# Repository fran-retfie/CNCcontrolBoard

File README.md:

# CNCcontrolBoard
CNC Control and Pendant Board with USB, RS485, SDCARD and LCD

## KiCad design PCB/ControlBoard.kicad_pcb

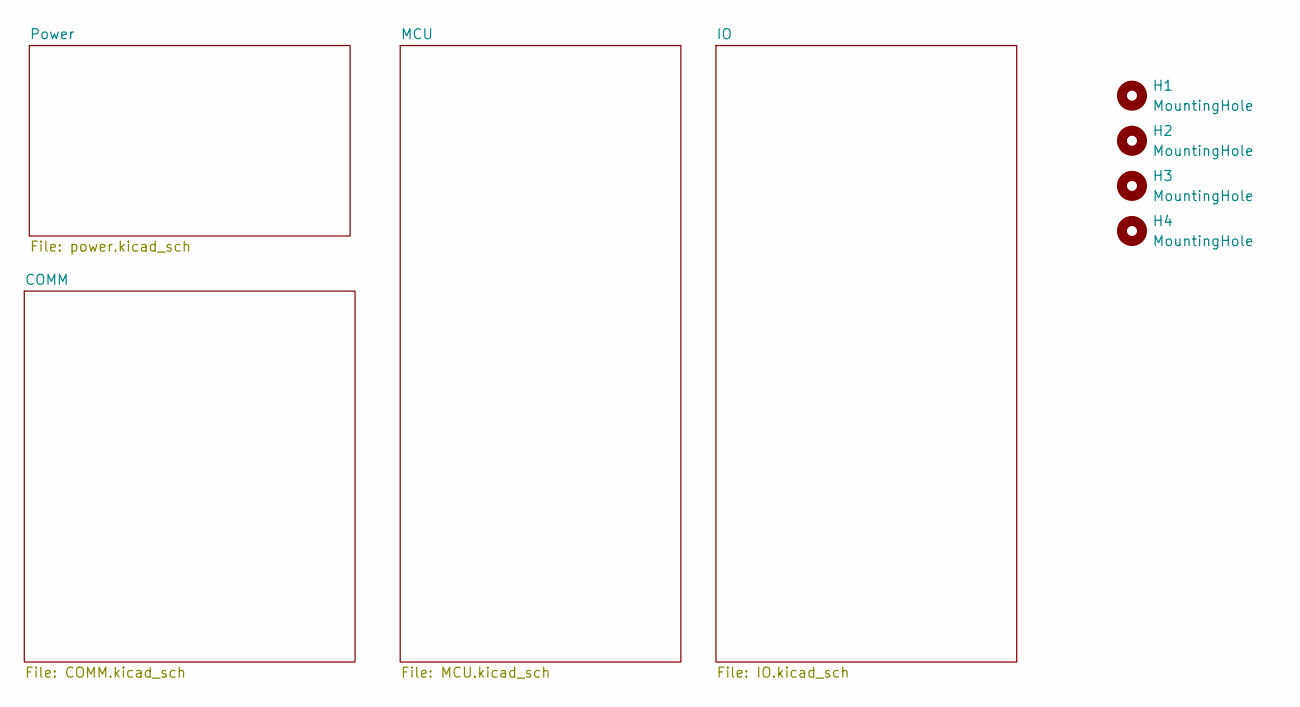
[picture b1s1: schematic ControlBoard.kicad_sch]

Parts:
H1, H2, H3, H4: MountingHole; MountingHole_3.2mm_M3_ISO14580_Pad

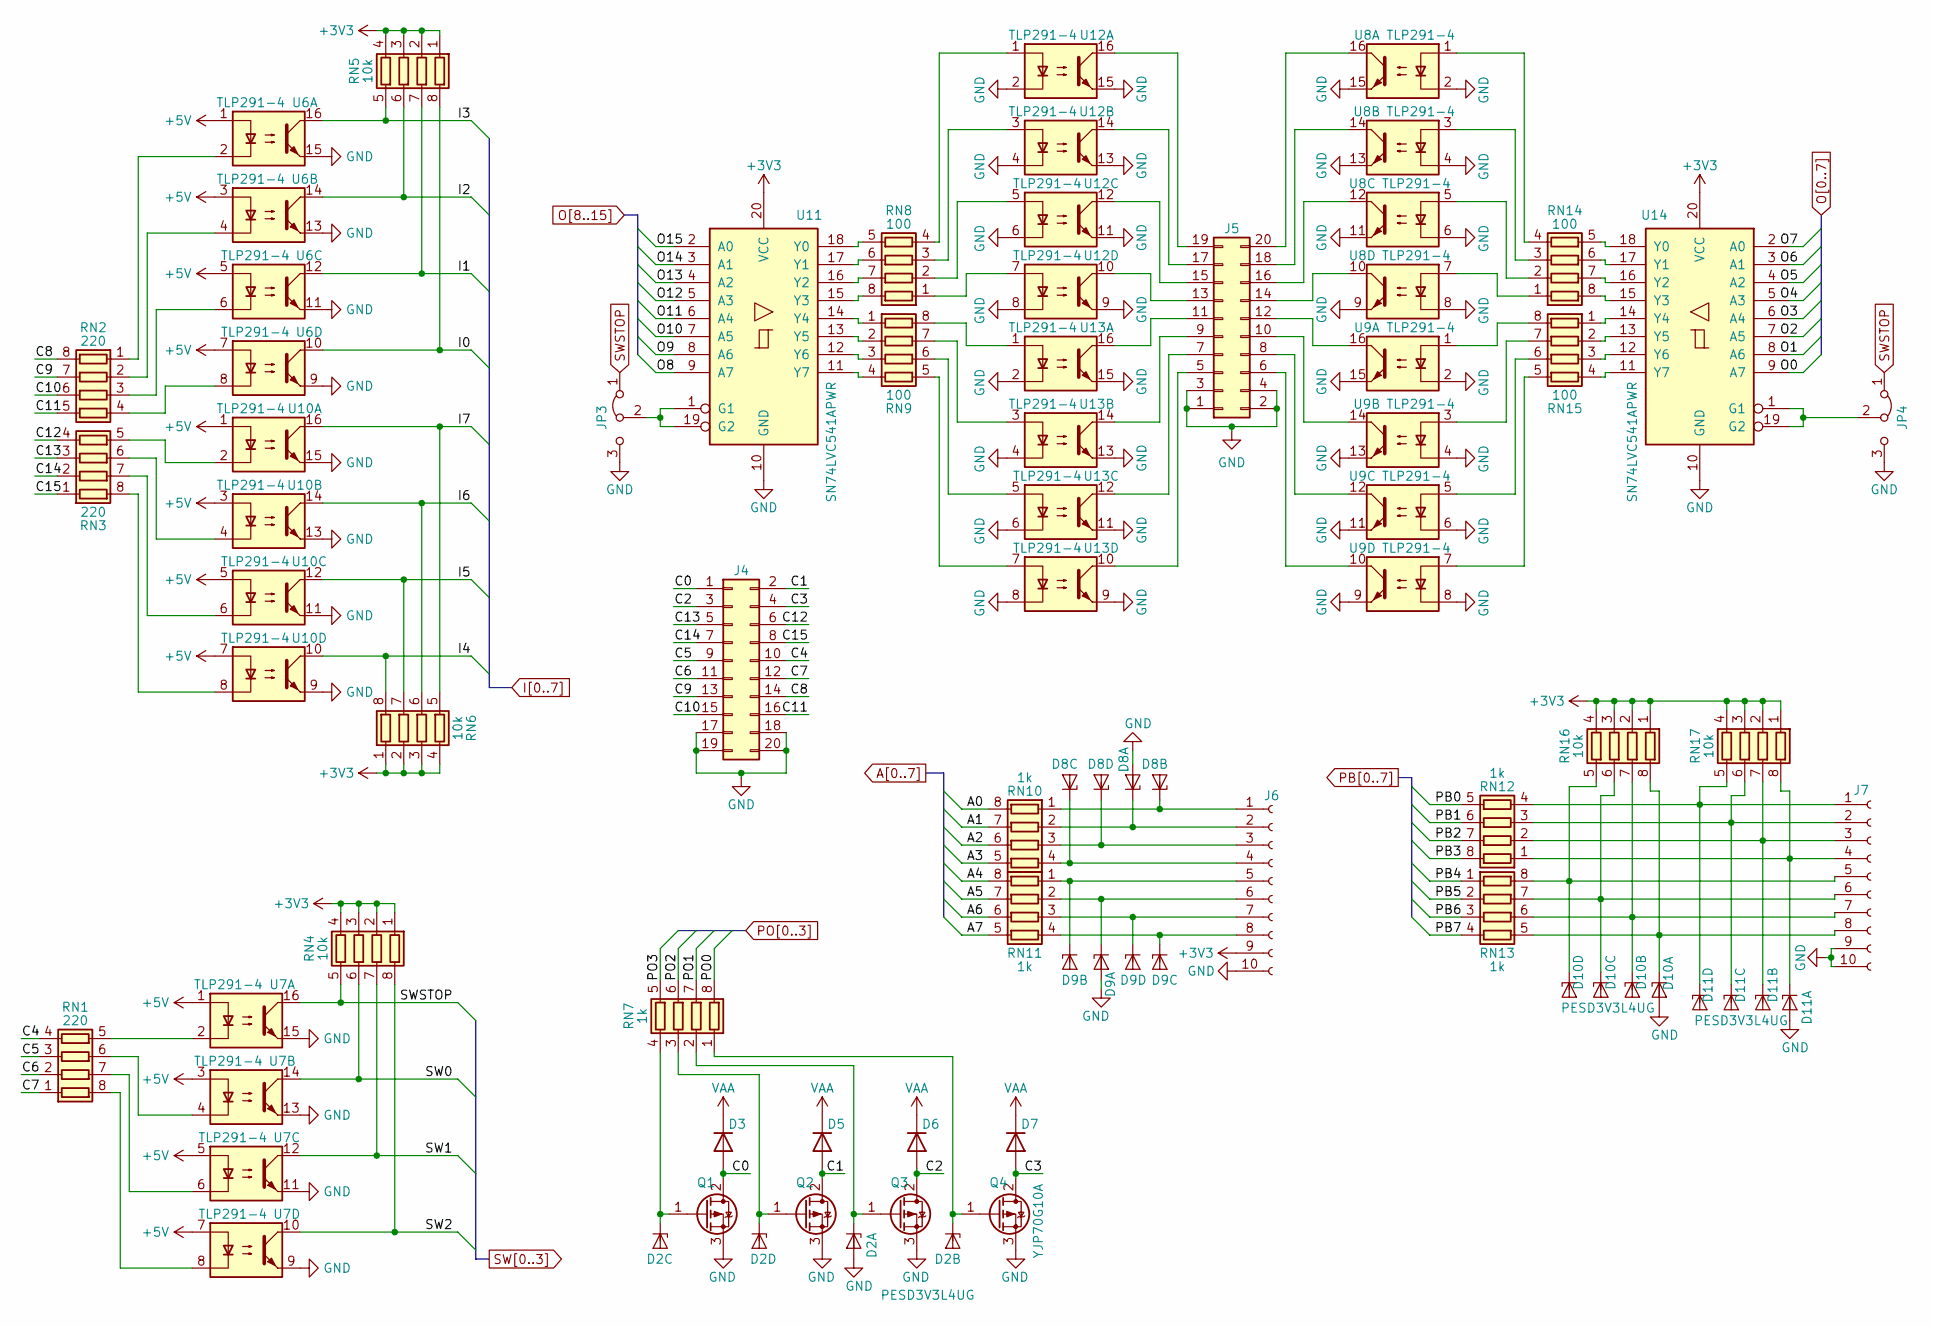
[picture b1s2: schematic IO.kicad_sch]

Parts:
D2, D10, D11: PESD3V3L4UG; SOT-353_SC-70-5; LCSC C3021134
D3, D5, D6, D7: M7; D_SMA; LCSC C95872
D8, D9: w; SOT-353_SC-70-5; LCSC C3021134
J4, J5: Conn_02x10_Odd_Even; DIP-20_500_ELL; LCSC C48336
J6, J7: Conn_01x10_Female; PinHeader_2x05_P2.54mm_Vertical
JP3: Jumper_3_Bridged12; SolderJumper-3_P1.3mm_Bridged12_RoundedPad1.0x1.5mm
JP4: Jumper_3_Bridged12; SolderJumper-3_P1.3mm_Bridged2Bar12_RoundedPad1.0x1.5mm
Q1, Q2, Q3, Q4: YJP70G10A; TO-220-3_Vertical
RN1, RN2, RN3: 220; R_Array_Concave_4x0603
RN4, RN5, RN6, RN16, RN17: 10k; R_Array_Concave_4x0603
RN7, RN10, RN11, RN12, RN13: 1k; R_Array_Concave_4x0603
RN8, RN9, RN14, RN15: 100; R_Array_Concave_4x0603
U6, U8, U9, U10, U12, U13: TLP291-4; SOIC-16_4.55x10.3mm_P1.27mm; LCSC C60900
U7: TLP291-4; SOIC-16_4.55x10.3mm_P1.27mm
U11, U14: SN74LVC541APWR; TSSOP-20_4.4x6.5mm_P0.65mm; LCSC C113281

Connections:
+3V3: J6.9, RN4.1 (R1.1), RN4.2 (R2.1), RN4.3 (R3.1), RN4.4 (R4.1), RN5.1 (R1.1), RN5.2 (R2.1), RN5.3 (R3.1), RN5.4 (R4.1), RN6.1 (R1.1), RN6.2 (R2.1), RN6.3 (R3.1), RN6.4 (R4.1), RN16.1 (R1.1), RN16.2 (R2.1), RN16.3 (R3.1), RN16.4 (R4.1), RN17.1 (R1.1), RN17.2 (R2.1), RN17.3 (R3.1), RN17.4 (R4.1), U11.20 (VCC), U14.20 (VCC); also elsewhere on the board
+5V: U6.1, U6.3, U6.5, U6.7, U7.1, U7.3, U7.5, U7.7, U10.1, U10.3, U10.5, U10.7; also elsewhere on the board
/IO/C0: D3.2 (A), J4.1, Q1.2 (D)
/IO/C1: D5.2 (A), J4.2, Q2.2 (D)
/IO/C2: D6.2 (A), J4.3, Q3.2 (D)
/IO/C3: D7.2 (A), J4.4, Q4.2 (D)
/IO/C4: J4.10, RN1.4 (R4.1)
/IO/C5: J4.9, RN1.3 (R3.1)
/IO/C6: J4.11, RN1.2 (R2.1)
/IO/C7: J4.12, RN1.1 (R1.1)
/IO/C8: J4.14, RN2.8 (R1.2)
/IO/C9: J4.13, RN2.7 (R2.2)
/IO/C10: J4.15, RN2.6 (R3.2)
/IO/C11: J4.16, RN2.5 (R4.2)
/IO/C12: J4.6, RN3.4 (R4.1)
/IO/C13: J4.5, RN3.3 (R3.1)
/IO/C14: J4.7, RN3.2 (R2.1)
/IO/C15: J4.8, RN3.1 (R1.1)
A0: RN10.8 (R1.2); also elsewhere on the board
A1: RN10.7 (R2.2); also elsewhere on the board
A2: RN10.6 (R3.2); also elsewhere on the board
A3: RN10.5 (R4.2); also elsewhere on the board
A4: RN11.8 (R1.2); also elsewhere on the board
A5: RN11.7 (R2.2); also elsewhere on the board
A6: RN11.6 (R3.2); also elsewhere on the board
A7: RN11.5 (R4.2); also elsewhere on the board
GND: D2.2 (A), D8.2 (A), D9.2 (A), D10.2 (A), D11.2 (A), J4.17, J4.18, J4.19, J4.20, J5.1, J5.2, J5.3, J5.4, J6.10, J7.9, J7.10, JP3.3 (B), JP4.3 (B), Q1.3 (S), Q2.3 (S), Q3.3 (S), Q4.3 (S), U6.9, U6.11, U6.13, U6.15, U7.9, U7.11, U7.13, U7.15, U8.2, U8.4, U8.6, U8.8, U8.9, U8.11, U8.13, U8.15, U9.2, U9.4, U9.6, U9.8, U9.9, U9.11, U9.13, U9.15, U10.9, U10.11, U10.13, U10.15, U11.10 (GND), U12.2, U12.4, U12.6, U12.8, U12.9, U12.11, U12.13, U12.15, U13.2, U13.4, U13.6, U13.8, U13.9, U13.11, U13.13, U13.15, U14.10 (GND); also elsewhere on the board
I0: RN5.8 (R1.2), U6.10; also elsewhere on the board
I1: RN5.7 (R2.2), U6.12; also elsewhere on the board
I2: RN5.6 (R3.2), U6.14; also elsewhere on the board
I3: RN5.5 (R4.2), U6.16; also elsewhere on the board
I4: RN6.8 (R1.2), U10.10; also elsewhere on the board
I5: RN6.7 (R2.2), U10.12; also elsewhere on the board
I6: RN6.6 (R3.2), U10.14; also elsewhere on the board
I7: RN6.5 (R4.2), U10.16; also elsewhere on the board
unnamed: D2.1 (K1), Q3.1 (G), RN7.2 (R2.1)
unnamed: D2.3 (K2), Q4.1 (G), RN7.1 (R1.1)
unnamed: D2.4 (K3), Q1.1 (G), RN7.4 (R4.1)
unnamed: D2.5 (K4), Q2.1 (G), RN7.3 (R3.1)
unnamed: D8.1 (K1), J6.2, RN10.2 (R2.1)
unnamed: D8.3 (K2), J6.1, RN10.1 (R1.1)
unnamed: D8.4 (K3), J6.4, RN10.4 (R4.1)
unnamed: D8.5 (K4), J6.3, RN10.3 (R3.1)
unnamed: D9.1 (K1), J6.6, RN11.2 (R2.1)
unnamed: D9.3 (K2), J6.5, RN11.1 (R1.1)
unnamed: D9.4 (K3), J6.8, RN11.4 (R4.1)
unnamed: D9.5 (K4), J6.7, RN11.3 (R3.1)
unnamed: D10.1 (K1), J7.8, RN13.5 (R4.2), RN16.8 (R1.2)
unnamed: D10.3 (K2), J7.7, RN13.6 (R3.2), RN16.7 (R2.2)
unnamed: D10.4 (K3), J7.6, RN13.7 (R2.2), RN16.6 (R3.2)
unnamed: D10.5 (K4), J7.5, RN13.8 (R1.2), RN16.5 (R4.2)
unnamed: D11.1 (K1), J7.4, RN12.1 (R1.1), RN17.8 (R1.2)
unnamed: D11.3 (K2), J7.3, RN12.2 (R2.1), RN17.7 (R2.2)
unnamed: D11.4 (K3), J7.2, RN12.3 (R3.1), RN17.6 (R3.2)
unnamed: D11.5 (K4), J7.1, RN12.4 (R4.1), RN17.5 (R4.2)
unnamed: J5.5, U13.10
unnamed: J5.6, U9.10
unnamed: J5.7, U13.12
unnamed: J5.8, U9.12
unnamed: J5.9, U13.14
unnamed: J5.10, U9.14
unnamed: J5.11, U13.16
unnamed: J5.12, U9.16
unnamed: J5.13, U12.10
unnamed: J5.14, U8.10
unnamed: J5.15, U12.12
unnamed: J5.16, U8.12
unnamed: J5.17, U12.14
unnamed: J5.18, U8.14
unnamed: J5.19, U12.16
unnamed: J5.20, U8.16
unnamed: JP3.2 (C), U11.1 (G1), U11.19 (G2)
unnamed: JP4.2 (C), U14.1 (G1), U14.19 (G2)
unnamed: RN1.5 (R4.2), U7.2
unnamed: RN1.6 (R3.2), U7.4
unnamed: RN1.7 (R2.2), U7.6
unnamed: RN1.8 (R1.2), U7.8
unnamed: RN2.1 (R1.1), U6.2
unnamed: RN2.2 (R2.1), U6.4
unnamed: RN2.3 (R3.1), U6.6
unnamed: RN2.4 (R4.1), U6.8
unnamed: RN3.5 (R4.2), U10.2
unnamed: RN3.6 (R3.2), U10.4
unnamed: RN3.7 (R2.2), U10.6
unnamed: RN3.8 (R1.2), U10.8
unnamed: RN8.1 (R1.1), U12.7
unnamed: RN8.2 (R2.1), U12.5
unnamed: RN8.3 (R3.1), U12.3
unnamed: RN8.4 (R4.1), U12.1
unnamed: RN8.5 (R4.2), U11.18 (Y0)
unnamed: RN8.6 (R3.2), U11.17 (Y1)
unnamed: RN8.7 (R2.2), U11.16 (Y2)
unnamed: RN8.8 (R1.2), U11.15 (Y3)
unnamed: RN9.1 (R1.1), U11.14 (Y4)
unnamed: RN9.2 (R2.1), U11.13 (Y5)
unnamed: RN9.3 (R3.1), U11.12 (Y6)
unnamed: RN9.4 (R4.1), U11.11 (Y7)
unnamed: RN9.5 (R4.2), U13.7
unnamed: RN9.6 (R3.2), U13.5
unnamed: RN9.7 (R2.2), U13.3
unnamed: RN9.8 (R1.2), U13.1
unnamed: RN14.1 (R1.1), U8.7
unnamed: RN14.2 (R2.1), U8.5
unnamed: RN14.3 (R3.1), U8.3
unnamed: RN14.4 (R4.1), U8.1
unnamed: RN14.5 (R4.2), U14.18 (Y0)
unnamed: RN14.6 (R3.2), U14.17 (Y1)
unnamed: RN14.7 (R2.2), U14.16 (Y2)
unnamed: RN14.8 (R1.2), U14.15 (Y3)
unnamed: RN15.1 (R1.1), U14.14 (Y4)
unnamed: RN15.2 (R2.1), U14.13 (Y5)
unnamed: RN15.3 (R3.1), U14.12 (Y6)
unnamed: RN15.4 (R4.1), U14.11 (Y7)
unnamed: RN15.5 (R4.2), U9.7
unnamed: RN15.6 (R3.2), U9.5
unnamed: RN15.7 (R2.2), U9.3
unnamed: RN15.8 (R1.2), U9.1
O0: U14.9 (A7); also elsewhere on the board
O1: U14.8 (A6); also elsewhere on the board
O2: U14.7 (A5); also elsewhere on the board
O3: U14.6 (A4); also elsewhere on the board
O4: U14.5 (A3); also elsewhere on the board
O5: U14.4 (A2); also elsewhere on the board
O6: U14.3 (A1); also elsewhere on the board
O7: U14.2 (A0); also elsewhere on the board
O8: U11.9 (A7); also elsewhere on the board
O9: U11.8 (A6); also elsewhere on the board
O10: U11.7 (A5); also elsewhere on the board
O11: U11.6 (A4); also elsewhere on the board
O12: U11.5 (A3); also elsewhere on the board
O13: U11.4 (A2); also elsewhere on the board
O14: U11.3 (A1); also elsewhere on the board
O15: U11.2 (A0); also elsewhere on the board
PB0: RN12.5 (R4.2); also elsewhere on the board
PB1: RN12.6 (R3.2); also elsewhere on the board
PB2: RN12.7 (R2.2); also elsewhere on the board
PB3: RN12.8 (R1.2); also elsewhere on the board
PB4: RN13.1 (R1.1); also elsewhere on the board
PB5: RN13.2 (R2.1); also elsewhere on the board
PB6: RN13.3 (R3.1); also elsewhere on the board
PB7: RN13.4 (R4.1); also elsewhere on the board
PO0: RN7.8 (R1.2); also elsewhere on the board
PO1: RN7.7 (R2.2); also elsewhere on the board
PO2: RN7.6 (R3.2); also elsewhere on the board
PO3: RN7.5 (R4.2); also elsewhere on the board
SW0: RN4.6 (R3.2), U7.14; also elsewhere on the board
SW1: RN4.7 (R2.2), U7.12; also elsewhere on the board
SW2: RN4.8 (R1.2), U7.10; also elsewhere on the board
SWSTOP: JP3.1 (A), JP4.1 (A), RN4.5 (R4.2), U7.16; also elsewhere on the board
VAA: D3.1 (K), D5.1 (K), D6.1 (K), D7.1 (K); also elsewhere on the board

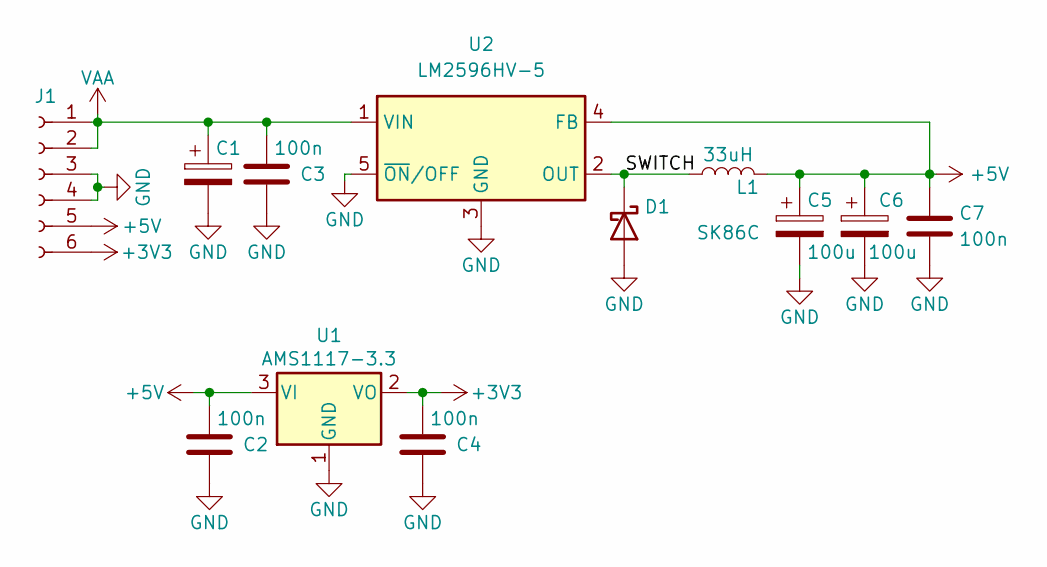
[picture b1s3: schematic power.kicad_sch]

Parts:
C1: C_Polarized; CP_Elec_6.3x7.7
C2, C3, C4, C7: 100n; C_0603_1608Metric
C5, C6: 100u; CP_Elec_6.3x7.7
D1: SK86C; D_SMC
J1: Conn_01x06_Female; PhoenixContact_MSTBA_2,5_6-G-5,08_1x06_P5.08mm_Horizontal; LCSC C505828
L1: 33uH; L_12x12mm_H8mm; LCSC C328259
U1: AMS1117-3.3; SOT-223-3_TabPin2; LCSC C6186
U2: LM2596HV-5; TO-263-5_TabPin3; LCSC C347421

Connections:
+3V3: C4.1, J1.6, U1.2 (VO); also elsewhere on the board
+5V: C2.1, C5.1, C6.1, C7.1, J1.5, L1.2, U1.3 (VI), U2.4 (FB); also elsewhere on the board
/Power/SWITCH: D1.1 (K), L1.1, U2.2 (OUT)
GND: C1.2, C2.2, C3.2, C4.2, C5.2, C6.2, C7.2, D1.2 (A), J1.3, J1.4, U1.1 (GND), U2.3 (GND), U2.5 (~ON/OFF); also elsewhere on the board
VAA: C1.1, C3.1, J1.1, J1.2, U2.1 (VIN); also elsewhere on the board

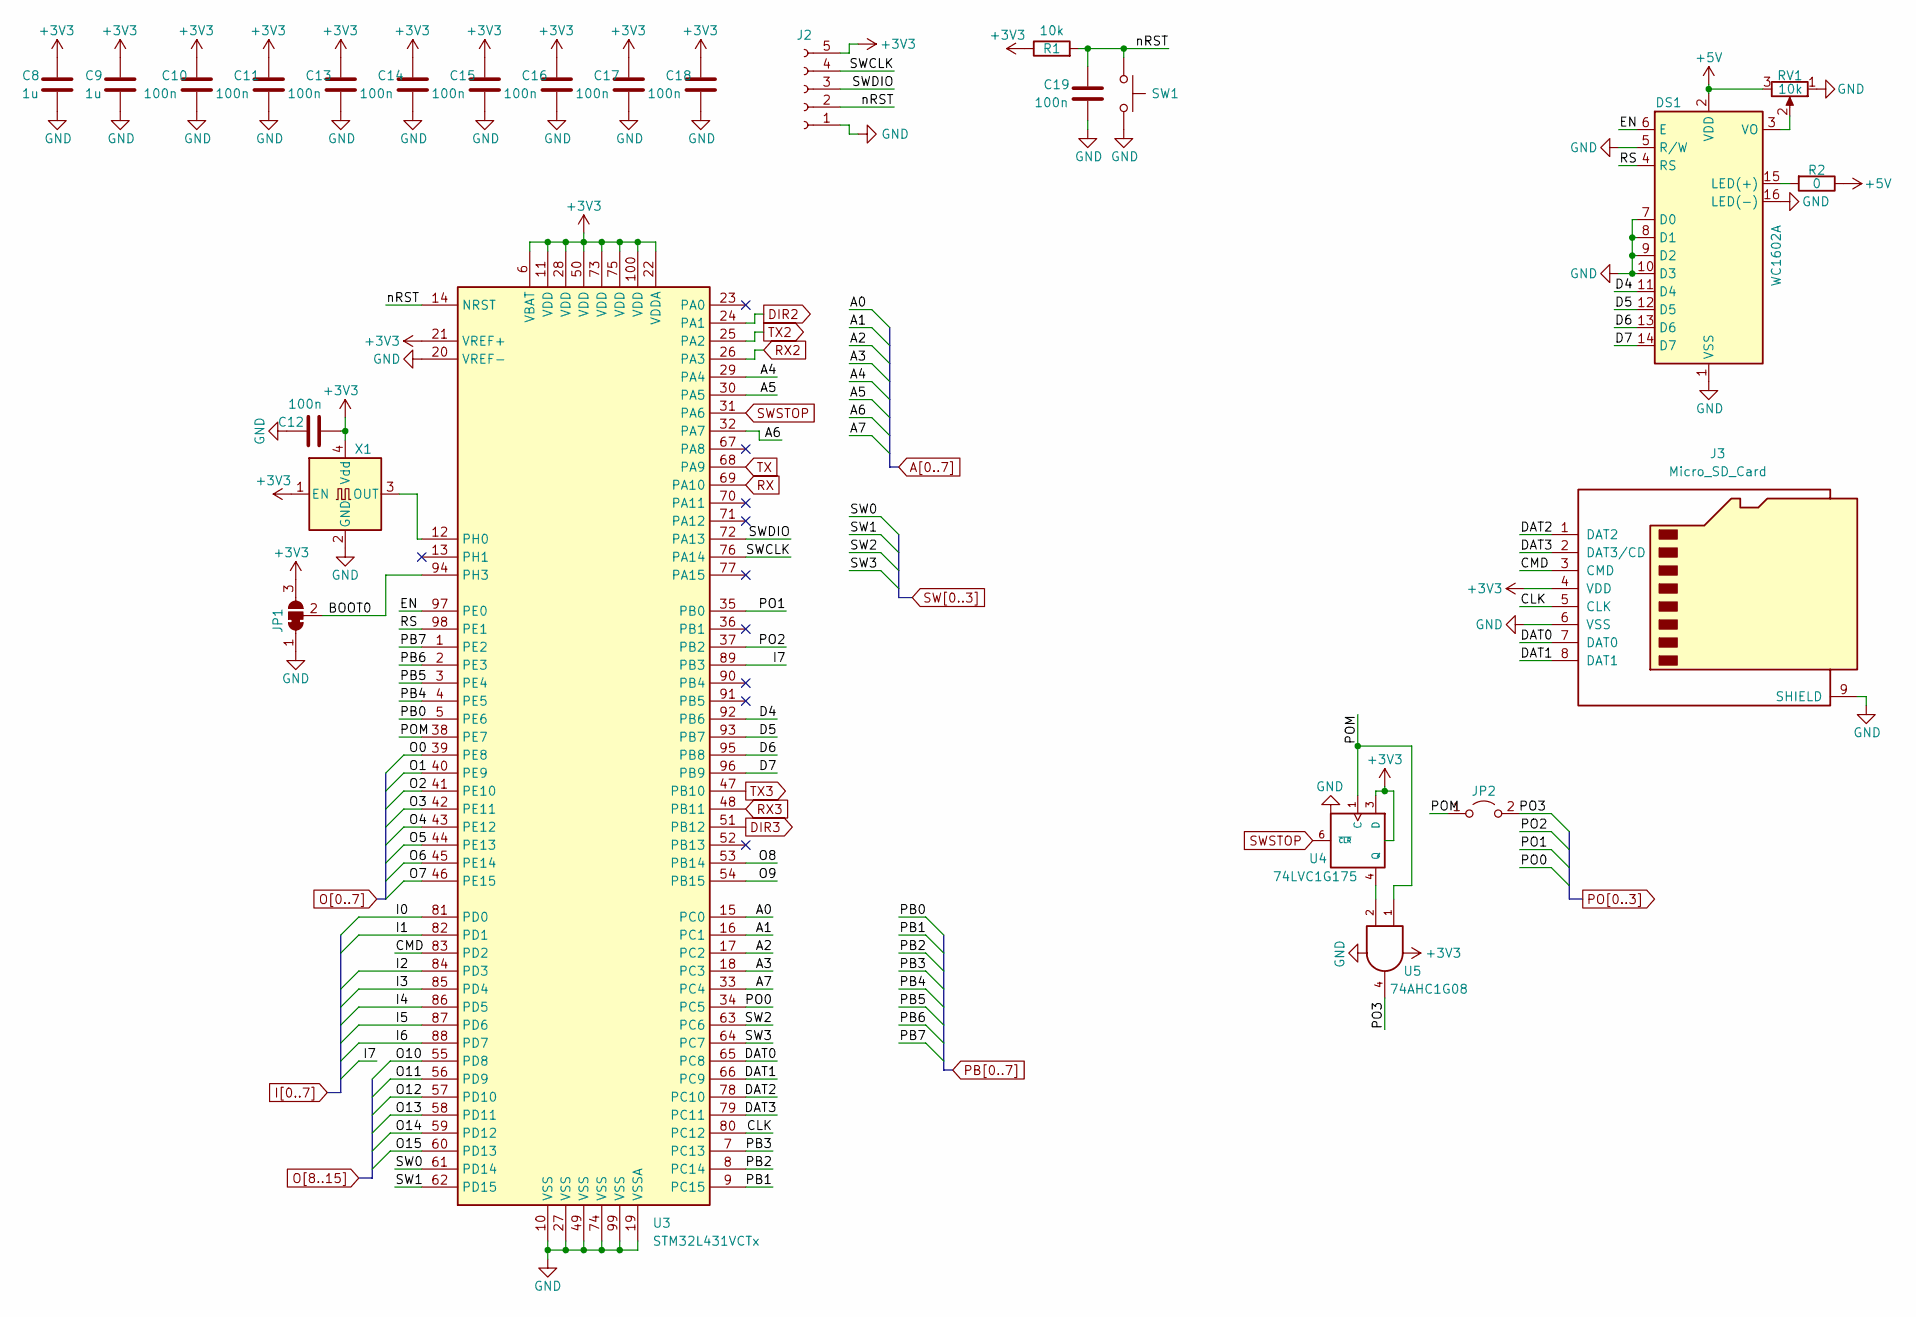
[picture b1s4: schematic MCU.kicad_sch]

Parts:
C8, C9: 1u; C_0603_1608Metric
C10, C11, C12, C13, C14, C15, C16, C17, C18, C19: 100n; C_0603_1608Metric
DS1: WC1602A
J2: Conn_01x05_Female; PinHeader_1x05_P2.54mm_Vertical
J3: Micro_SD_Card; microSD_HC_Molex_47219-2001
JP1: SolderJumper_3_Bridged12; SolderJumper-3_P1.3mm_Bridged2Bar12_Pad1.0x1.5mm_NumberLabe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
JP2: Jumper_2_Open; SolderJumper-2_P1.3mm_Open_RoundedPad1.0x1.5mm
R1: 10k; R_0603_1608Metric
R2: 0; R_0603_1608Metric
RV1: 10k; Potentiometer_Bourns_3386C_Horizontal
SW1: SW_Push; SW_SPST_B3SL-1002P
U3: STM32L431VCTx; LQFP-100_14x14mm_P0.5mm; LCSC C455384
U4: 74LVC1G175; SOT-363_SC-70-6; LCSC C202238
U5: 74AHC1G08; SOT-353_SC-70-5; LCSC C12490
X1: ASE-xxxMHz; Oscillator_SMD_Abracon_ASE-4Pin_3.2x2.5mm

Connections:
+3V3: C8.1, C9.1, C10.1, C11.1, C12.1, C13.1, C14.1, C15.1, C16.1, C17.1, C18.1, J2.5, J3.4 (VDD), JP1.3 (B), R1.1, U3.6 (VBAT), U3.11 (VDD), U3.21 (VREF+), U3.22 (VDDA), U3.28 (VDD), U3.50 (VDD), U3.73 (VDD), U3.75 (VDD), U3.100 (VDD), U4.3 (D), U4.5 (VCC), U5.5 (VCC), X1.1 (EN), X1.4 (Vdd); also elsewhere on the board
+5V: DS1.2 (VDD), R2.1, RV1.3; also elsewhere on the board
/MCU/BOOT0: JP1.2 (C), U3.94 (PH3)
/MCU/CLK: J3.5 (CLK), U3.80 (PC12)
/MCU/CMD: J3.3 (CMD), U3.83 (PD2)
/MCU/D4: DS1.11 (D4), U3.92 (PB6)
/MCU/D5: DS1.12 (D5), U3.93 (PB7)
/MCU/D6: DS1.13 (D6), U3.95 (PB8)
/MCU/D7: DS1.14 (D7), U3.96 (PB9)
/MCU/DAT0: J3.7 (DAT0), U3.65 (PC8)
/MCU/DAT1: J3.8 (DAT1), U3.66 (PC9)
/MCU/DAT2: J3.1 (DAT2), U3.78 (PC10)
/MCU/DAT3: J3.2 (DAT3/CD), U3.79 (PC11)
/MCU/EN: DS1.6 (E), U3.97 (PE0)
/MCU/POM: JP2.1 (A), U3.38 (PE7), U4.1 (C), U5.1
/MCU/RS: DS1.4 (RS), U3.98 (PE1)
/MCU/SWCLK: J2.4, U3.76 (PA14)
/MCU/SWDIO: J2.3, U3.72 (PA13)
/MCU/nRST: C19.1, J2.2, R1.2, SW1.1, U3.14 (NRST)
A0: U3.15 (PC0); also elsewhere on the board
A1: U3.16 (PC1); also elsewhere on the board
A2: U3.17 (PC2); also elsewhere on the board
A3: U3.18 (PC3); also elsewhere on the board
A4: U3.29 (PA4); also elsewhere on the board
A5: U3.30 (PA5); also elsewhere on the board
A6: U3.32 (PA7); also elsewhere on the board
A7: U3.33 (PC4); also elsewhere on the board
DIR2: U3.24 (PA1); also elsewhere on the board
DIR3: U3.51 (PB12); also elsewhere on the board
GND: C8.2, C9.2, C10.2, C11.2, C12.2, C13.2, C14.2, C15.2, C16.2, C17.2, C18.2, C19.2, DS1.1 (VSS), DS1.5 (R/W), DS1.7 (D0), DS1.8 (D1), DS1.9 (D2), DS1.10 (D3), DS1.16 (LED(-)), J2.1, J3.6 (VSS), J3.9 (SHIELD), JP1.1 (A), RV1.1, SW1.2, U3.10 (VSS), U3.19 (VSSA), U3.20 (VREF-), U3.27 (VSS), U3.49 (VSS), U3.74 (VSS), U3.99 (VSS), U4.2 (GND), U5.3 (GND), X1.2 (GND); also elsewhere on the board
I0: U3.81 (PD0); also elsewhere on the board
I1: U3.82 (PD1); also elsewhere on the board
I2: U3.84 (PD3); also elsewhere on the board
I3: U3.85 (PD4); also elsewhere on the board
I4: U3.86 (PD5); also elsewhere on the board
I5: U3.87 (PD6); also elsewhere on the board
I6: U3.88 (PD7); also elsewhere on the board
I7: U3.89 (PB3); also elsewhere on the board
unnamed: DS1.3 (VO), RV1.2
unnamed: DS1.15 (LED(+)), R2.2
unnamed: U3.12 (PH0), X1.3 (OUT)
unnamed: U4.4 (Q), U5.2
O0: U3.39 (PE8); also elsewhere on the board
O1: U3.40 (PE9); also elsewhere on the board
O2: U3.41 (PE10); also elsewhere on the board
O3: U3.42 (PE11); also elsewhere on the board
O4: U3.43 (PE12); also elsewhere on the board
O5: U3.44 (PE13); also elsewhere on the board
O6: U3.45 (PE14); also elsewhere on the board
O7: U3.46 (PE15); also elsewhere on the board
O8: U3.53 (PB14); also elsewhere on the board
O9: U3.54 (PB15); also elsewhere on the board
O10: U3.55 (PD8); also elsewhere on the board
O11: U3.56 (PD9); also elsewhere on the board
O12: U3.57 (PD10); also elsewhere on the board
O13: U3.58 (PD11); also elsewhere on the board
O14: U3.59 (PD12); also elsewhere on the board
O15: U3.60 (PD13); also elsewhere on the board
PB0: U3.5 (PE6); also elsewhere on the board
PB1: U3.9 (PC15); also elsewhere on the board
PB2: U3.8 (PC14); also elsewhere on the board
PB3: U3.7 (PC13); also elsewhere on the board
PB4: U3.4 (PE5); also elsewhere on the board
PB5: U3.3 (PE4); also elsewhere on the board
PB6: U3.2 (PE3); also elsewhere on the board
PB7: U3.1 (PE2); also elsewhere on the board
PO0: U3.34 (PC5); also elsewhere on the board
PO1: U3.35 (PB0); also elsewhere on the board
PO2: U3.37 (PB2); also elsewhere on the board
PO3: JP2.2 (B), U5.4; also elsewhere on the board
RX: U3.69 (PA10); also elsewhere on the board
RX2: U3.26 (PA3); also elsewhere on the board
RX3: U3.48 (PB11); also elsewhere on the board
SW0: U3.61 (PD14); also elsewhere on the board
SW1: U3.62 (PD15); also elsewhere on the board
SW2: U3.63 (PC6); also elsewhere on the board
SW3: U3.64 (PC7)
SWSTOP: U3.31 (PA6), U4.6 (~CLR); also elsewhere on the board
TX: U3.68 (PA9); also elsewhere on the board
TX2: U3.25 (PA2); also elsewhere on the board
TX3: U3.47 (PB10); also elsewhere on the board

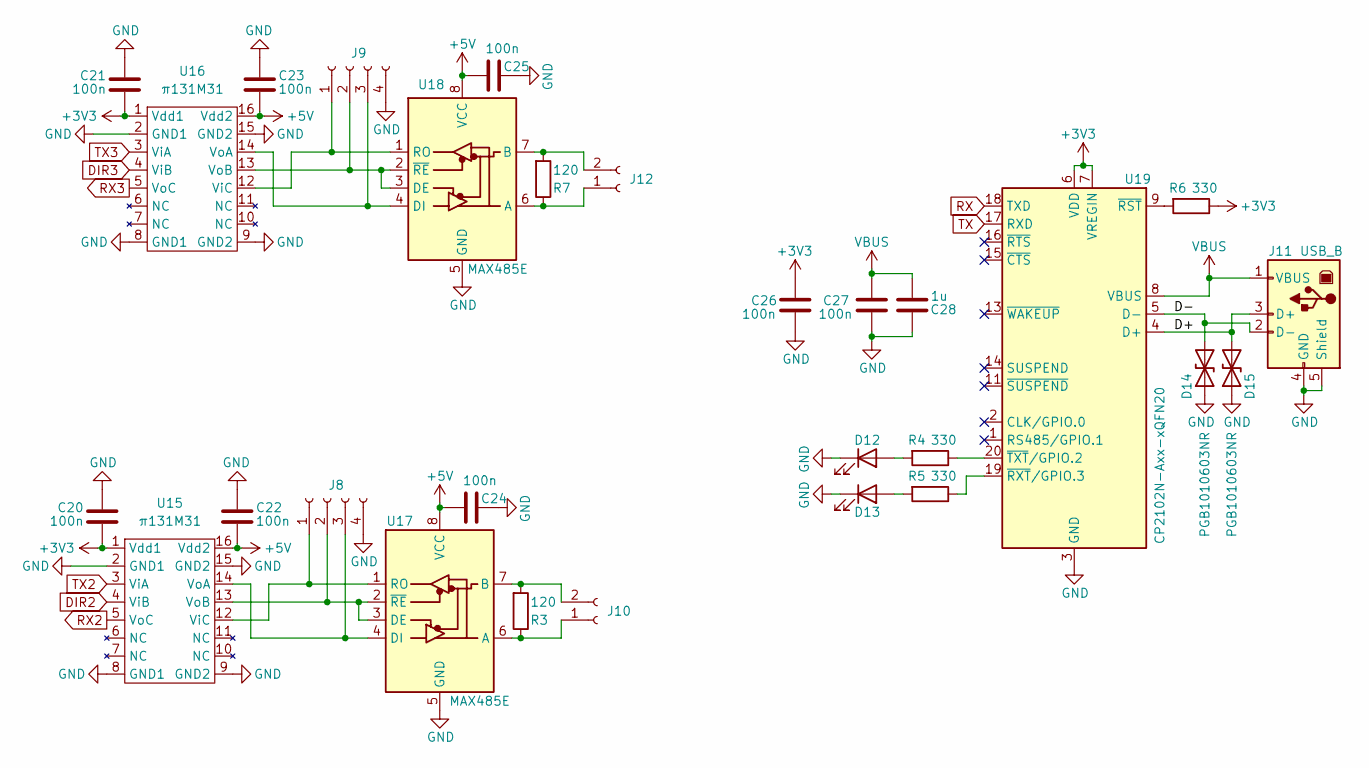
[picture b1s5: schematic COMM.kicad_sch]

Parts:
C20, C21, C22, C23, C24, C25, C26, C27: 100n; C_0603_1608Metric
C28: 1u; C_0603_1608Metric
D12, D13: LED; LED_0805_2012Metric
D14, D15: PGB1010603NR; D_0603_1608Metric; LCSC C10677
J8, J9: Conn_01x04_Female; PinHeader_1x04_P2.54mm_Vertical
J10, J12: Conn_01x02_Female; PhoenixContact_MC_1,5_2-G-5.08_1x02_P5.08mm_Horizontal
J11: USB_B; USB_B_TE_5787834_Vertical
R3, R7: 120; R_0603_1608Metric
R4, R5, R6: 330; R_0603_1608Metric
U15, U16: π131M31; SOIC-16_3.9x9.9mm_P1.27mm; LCSC C471599
U17, U18: MAX485E; SOP-8_3.9x4.9mm_P1.27mm; LCSC C2960453
U19: CP2102N-Axx-xQFN20; SiliconLabs_QFN-20-1EP_3x3mm_P0.5mm_EP1.8x1.8mm

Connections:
+3V3: C20.2, C21.2, C26.1, R6.1, U15.1 (Vdd1), U16.1 (Vdd1), U19.6 (VDD), U19.7 (VREGIN); also elsewhere on the board
+5V: C22.2, C23.2, C24.2, C25.2, U15.16 (Vdd2), U16.16 (Vdd2), U17.8 (VCC), U18.8 (VCC); also elsewhere on the board
/COMM/D+: D15.2 (A2), J11.3 (D+), U19.4 (D+)
/COMM/D-: D14.2 (A2), J11.2 (D-), U19.5 (D-)
DIR2: U15.4 (ViB); also elsewhere on the board
DIR3: U16.4 (ViB); also elsewhere on the board
GND: C20.1, C21.1, C22.1, C23.1, C24.1, C25.1, C26.2, C27.2, C28.1, D12.1 (K), D13.1 (K), D14.1 (A1), D15.1 (A1), J8.4, J9.4, J11.4 (GND), J11.5 (Shield), U15.2 (GND1), U15.8 (GND1), U15.9 (GND2), U15.15 (GND2), U16.2 (GND1), U16.8 (GND1), U16.9 (GND2), U16.15 (GND2), U17.5 (GND), U18.5 (GND), U19.3 (GND), U19.12 (GND), U19.21 (GND); also elsewhere on the board
unnamed: D12.2 (A), R4.2
unnamed: D13.2 (A), R5.2
unnamed: J8.1, U15.12 (ViC), U17.1 (RO)
unnamed: J8.2, U15.13 (VoB), U17.2 (~RE), U17.3 (DE)
unnamed: J8.3, U15.14 (VoA), U17.4 (DI)
unnamed: J9.1, U16.12 (ViC), U18.1 (RO)
unnamed: J9.2, U16.13 (VoB), U18.2 (~RE), U18.3 (DE)
unnamed: J9.3, U16.14 (VoA), U18.4 (DI)
unnamed: J10.1, R3.1, U17.6 (A)
unnamed: J10.2, R3.2, U17.7 (B)
unnamed: J12.1, R7.1, U18.6 (A)
unnamed: J12.2, R7.2, U18.7 (B)
unnamed: R4.1, U19.20 (~TXT/GPIO.2)
unnamed: R5.1, U19.19 (~RXT/GPIO.3)
unnamed: R6.2, U19.9 (~RST)
RX: U19.18 (TXD); also elsewhere on the board
RX2: U15.5 (VoC); also elsewhere on the board
RX3: U16.5 (VoC); also elsewhere on the board
TX: U19.17 (RXD); also elsewhere on the board
TX2: U15.3 (ViA); also elsewhere on the board
TX3: U16.3 (ViA); also elsewhere on the board
VBUS: C27.1, C28.2, J11.1 (VBUS), U19.8 (VBUS)

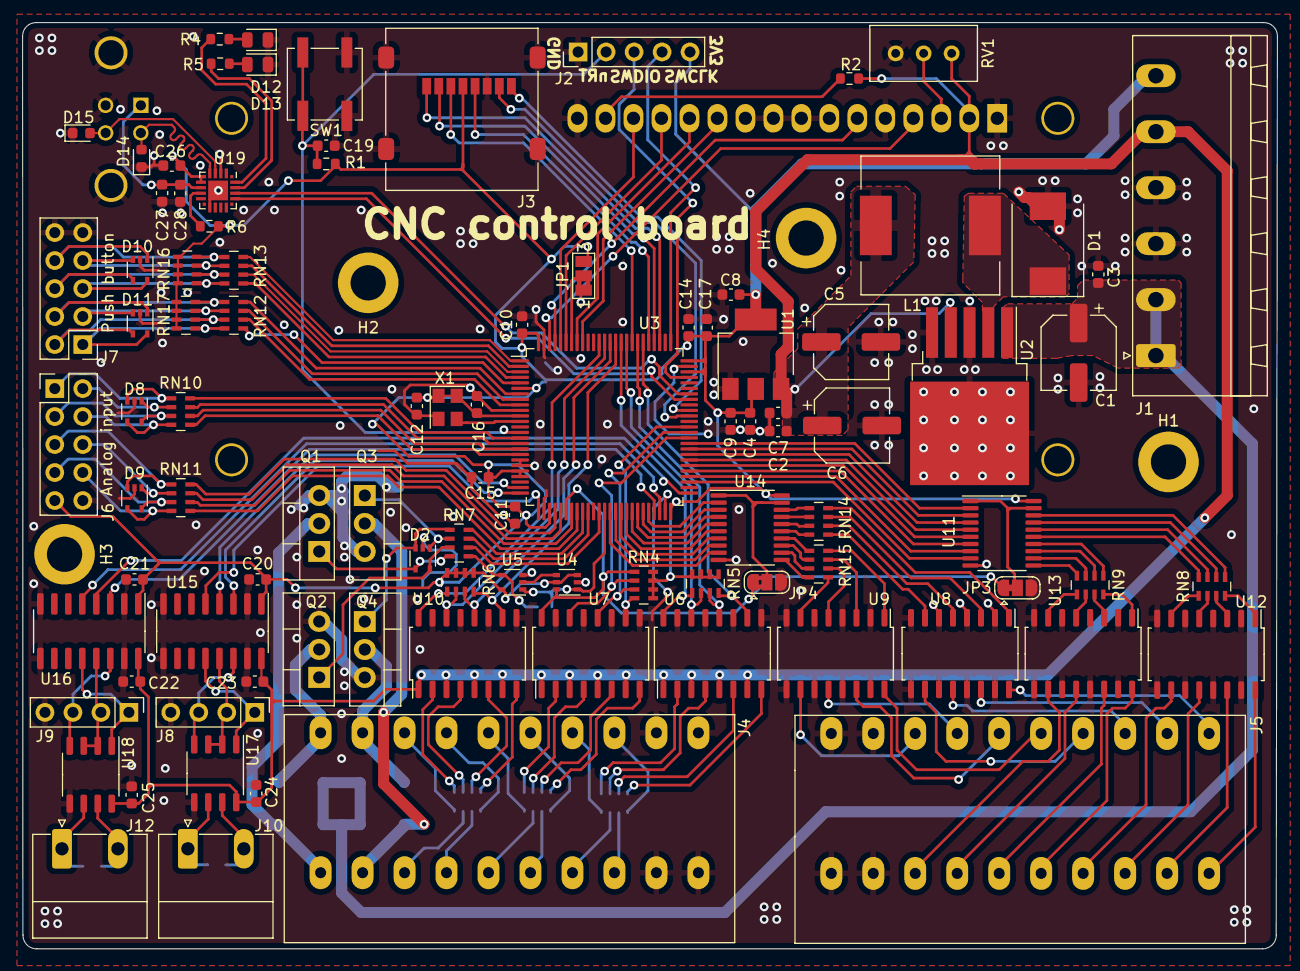
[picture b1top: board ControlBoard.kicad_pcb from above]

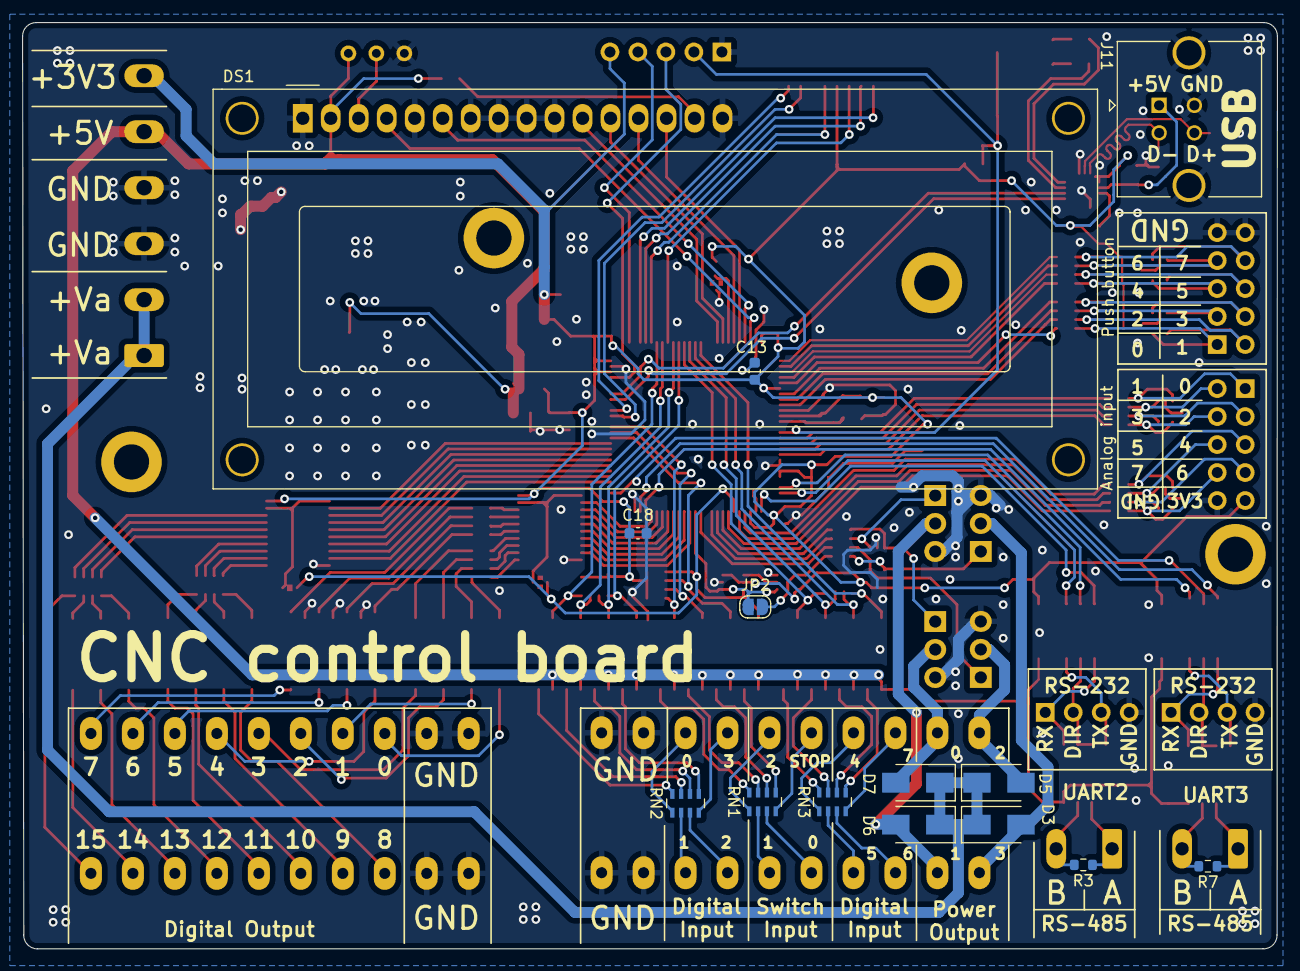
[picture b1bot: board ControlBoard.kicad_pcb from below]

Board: 2 copper layers, 113.9 x 84.1 mm, 114 parts (14 on the bottom side), 198 nets.

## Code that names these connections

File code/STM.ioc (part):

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Mcu.Name=STM32L431VCTx
Mcu.Package=LQFP100
Mcu.UserName=STM32L431VCTx
PA1.GPIOParameters=GPIO_Label
PA1.GPIO_Label=DIR2
PA1.Signal=GPIO_Output
PA10.Mode=Asynchronous
PA10.Signal=USART1_RX
PA13\ (JTMS-SWDIO).Signal=SYS_JTMS-SWDIO
PA14\ (JTCK-SWCLK).Signal=SYS_JTCK-SWCLK
PA2.Mode=Asynchronous
PA2.Signal=USART2_TX
PA3.Mode=Asynchronous
PA3.Signal=USART2_RX
PA4.GPIOParameters=GPIO_Label
PA4.GPIO_Label=A4
PA4.Signal=ADCx_IN9
PA5.GPIOParameters=GPIO_Label
PA5.GPIO_Label=A5
PA5.Signal=ADCx_IN10
PA6.GPIOParameters=GPIO_Label,GPIO_ModeDefaultEXTI
PA6.GPIO_Label=SWSTOP
PA6.GPIO_ModeDefaultEXTI=GPIO_MODE_IT_RISING
PA6.Signal=SharedStack_PA6
PA6.Stacked=true
PA7.GPIOParameters=GPIO_Label
PA7.GPIO_Label=A6
PA7.Signal=ADCx_IN12
PA9.Mode=Asynchronous
PA9.Signal=USART1_TX
PB0.GPIOParameters=GPIO_Label
PB0.GPIO_Label=PO1
PB0.Signal=GPIO_Output
PB10.Mode=Asynchronous
PB10.Signal=USART3_TX
PB11.Mode=Asynchronous
PB11.Signal=USART3_RX
PB12.GPIOParameters=GPIO_Label
PB12.GPIO_Label=DIR3
PB12.Signal=GPIO_Output
PB14.GPIOParameters=GPIO_Label
PB14.GPIO_Label=O8
PB14.Signal=S_TIM15_CH1
PB15.GPIOParameters=GPIO_Label
PB15.GPIO_Label=O9
PB15.Mode=PWM Generation3 CH3N
PB15.Signal=TIM1_CH3N
PB2.GPIOParameters=GPIO_Label
PB2.GPIO_Label=PO2
PB2.Signal=GPIO_Output
PB3\ (JTDO-TRACESWO).GPIOParameters=GPIO_Label
PB3\ (JTDO-TRACESWO).GPIO_Label=I7
PB3\ (JTDO-TRACESWO).Signal=GPIO_Input
PB6.GPIOParameters=GPIO_Label
PB6.GPIO_Label=D4
PB6.Signal=GPIO_Output
PB7.GPIOParameters=GPIO_Label
PB7.GPIO_Label=D5
PB7.Signal=GPIO_Output
PB8.GPIOParameters=GPIO_Label
PB8.GPIO_Label=D6
PB8.Signal=GPIO_Output
PB9.GPIOParameters=GPIO_Label
PB9.GPIO_Label=D7
PB9.Signal=GPIO_Output
PC0.GPIOParameters=GPIO_Label
PC0.GPIO_Label=A0
PC0.Signal=ADCx_IN1
PC1.GPIOParameters=GPIO_Label
PC1.GPIO_Label=A1
PC1.Signal=ADCx_IN2
PC10.Mode=SD_4_bits_Wide_bus
PC10.Signal=SDMMC1_D2
PC11.Mode=SD_4_bits_Wide_bus
PC11.Signal=SDMMC1_D3
PC12.Mode=SD_4_bits_Wide_bus
PC12.Signal=SDMMC1_CK
PC13.GPIOParameters=GPIO_Label
PC13.GPIO_Label=PB2
PC13.Signal=GPIO_Input
PC14-OSC32_IN\ (PC14).GPIOParameters=GPIO_Label
PC14-OSC32_IN\ (PC14).GPIO_Label=PB1
PC14-OSC32_IN\ (PC14).Signal=GPIO_Input
PC15-OSC32_OUT\ (PC15).GPIOParameters=GPIO_Label
PC15-OSC32_OUT\ (PC15).GPIO_Label=PB0
PC15-OSC32_OUT\ (PC15).Signal=GPIO_Input
PC2.GPIOParameters=GPIO_Label
PC2.GPIO_Label=A2
PC2.Signal=ADCx_IN3
PC3.GPIOParameters=GPIO_Label
PC3.GPIO_Label=A3
PC3.Signal=ADCx_IN4
PC4.GPIOParameters=GPIO_Label
PC4.GPIO_Label=A7
PC4.Signal=ADCx_IN13
PC5.GPIOParameters=GPIO_Label
PC5.GPIO_Label=PO0
PC5.Signal=GPIO_Output
PC6.GPIOParameters=GPIO_Label
PC6.GPIO_Label=SW2
PC6.Signal=GPIO_Output
PC8.Mode=SD_4_bits_Wide_bus
PC8.Signal=SDMMC1_D0
PC9.Mode=SD_4_bits_Wide_bus
PC9.Signal=SDMMC1_D1
PD0.GPIOParameters=GPIO_Label
PD0.GPIO_Label=I0
PD0.Signal=GPIO_Input
PD1.GPIOParameters=GPIO_Label
PD1.GPIO_Label=I1
PD1.Signal=GPIO_Input
PD10.GPIOParameters=GPIO_Label
PD10.GPIO_Label=O12
PD10.Signal=GPIO_Output
PD11.GPIOParameters=GPIO_Label
PD11.GPIO_Label=O13
PD11.Signal=GPIO_Output
PD12.GPIOParameters=GPIO_Label
PD12.GPIO_Label=O14
PD12.Signal=GPIO_Output
PD13.GPIOParameters=GPIO_Label
PD13.GPIO_Label=O15
PD13.Signal=GPIO_Output
PD14.GPIOParameters=GPIO_Label,GPIO_ModeDefaultEXTI
PD14.GPIO_Label=SW0
PD14.GPIO_ModeDefaultEXTI=GPIO_MODE_IT_FALLING
PD14.Signal=GPXTI14
PD15.GPIOParameters=GPIO_Label,GPIO_ModeDefaultEXTI
PD15.GPIO_Label=SW1
PD15.GPIO_ModeDefaultEXTI=GPIO_MODE_IT_FALLING
PD15.Signal=GPXTI15
PD2.Mode=SD_4_bits_Wide_bus
PD2.Signal=SDMMC1_CMD
PD3.GPIOParameters=GPIO_Label
PD3.GPIO_Label=I2
PD3.Signal=GPIO_Input
PD4.GPIOParameters=GPIO_Label
PD4.GPIO_Label=I3
PD4.Signal=GPIO_Input
PD5.GPIOParameters=GPIO_Label
PD5.GPIO_Label=I4
PD5.Signal=GPIO_Input
PD6.GPIOParameters=GPIO_Label
PD6.GPIO_Label=I5
PD6.Signal=GPIO_Input
PD7.GPIOParameters=GPIO_Label
PD7.GPIO_Label=I6
PD7.Signal=GPIO_Input
PD8.GPIOParameters=GPIO_Label
PD8.GPIO_Label=O10
PD8.Signal=GPIO_Output
PD9.GPIOParameters=GPIO_Label
PD9.GPIO_Label=O11
PD9.Signal=GPIO_Output
PE0.GPIOParameters=GPIO_Label
PE0.GPIO_Label=EN
PE0.Signal=GPIO_Output
PE1.GPIOParameters=GPIO_Label
PE1.GPIO_Label=RS
PE1.Signal=GPIO_Output
PE10.GPIOParameters=GPIO_Label
PE10.GPIO_Label=O2
PE10.Signal=GPIO_Output
PE11.GPIOParameters=GPIO_Label
PE11.GPIO_Label=O3
PE11.Signal=GPIO_Output
PE12.GPIOParameters=GPIO_Label
PE12.GPIO_Label=O4
PE12.Signal=GPIO_Output
PE13.GPIOParameters=GPIO_Label
PE13.GPIO_Label=O5
PE13.Signal=GPIO_Output
PE14.GPIOParameters=GPIO_Label
PE14.GPIO_Label=O6
PE14.Signal=GPIO_Output
PE15.GPIOParameters=GPIO_Label
PE15.GPIO_Label=O7
PE15.Signal=GPIO_Output
PE2.GPIOParameters=GPIO_Label
PE2.GPIO_Label=PB7
PE2.Signal=GPIO_Input
PE3.GPIOParameters=GPIO_Label
PE3.GPIO_Label=PB6
PE3.Signal=GPIO_Input
PE4.GPIOParameters=GPIO_Label
PE4.GPIO_Label=PB5
PE4.Signal=GPIO_Input
PE5.GPIOParameters=GPIO_Label
PE5.GPIO_Label=PB4
PE5.Signal=GPIO_Input
PE6.GPIOParameters=GPIO_Label
PE6.GPIO_Label=PB3
PE6.Signal=GPIO_Input
PE7.GPIOParameters=GPIO_Label
PE7.GPIO_Label=PO3
PE7.Signal=GPIO_Output
PE8.GPIOParameters=GPIO_Label
PE8.GPIO_Label=O0
PE8.Signal=GPIO_Output
PE9.GPIOParameters=GPIO_Label
PE9.GPIO_Label=O1
PE9.Signal=GPIO_Output
PH0-OSC_IN\ (PH0).Mode=HSE-External-Clock-Source
PH0-OSC_IN\ (PH0).Signal=RCC_OSC_IN
RCC.HSE_VALUE=8000000
RCC.SYSCLKFreq_VALUE=48000000
board=custom

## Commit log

2022-12-14 PCB done and code first commit
2022-12-27 peripherals working
2023-01-04 something is working
2023-01-10 Stepper control and safety completed
2023-01-10 limit switches now working
2023-01-11 #1 test day edits
2023-01-15 TImer stuff corrected
2023-01-26 speed increase and some bugs solved
2023-01-29 test day 2 corrections
2023-02-02 modifica test 3
2023-02-02 feed rates now calculated using float
2023-02-21 removed build files
2023-02-21 removed build files 2
2023-02-21 Spindle control implemented
2023-02-25 updated zeroing procedure
2023-03-01 test day 4 bug corrections
2023-03-01 added facing mode 2
2023-03-04 New mode "points"
2023-03-04 alarm input implemented
2023-06-04 test day 5 fix & feedrate adjust
2023-06-04 test day 5 fix
2023-08-02 spindle control & homing after job done
